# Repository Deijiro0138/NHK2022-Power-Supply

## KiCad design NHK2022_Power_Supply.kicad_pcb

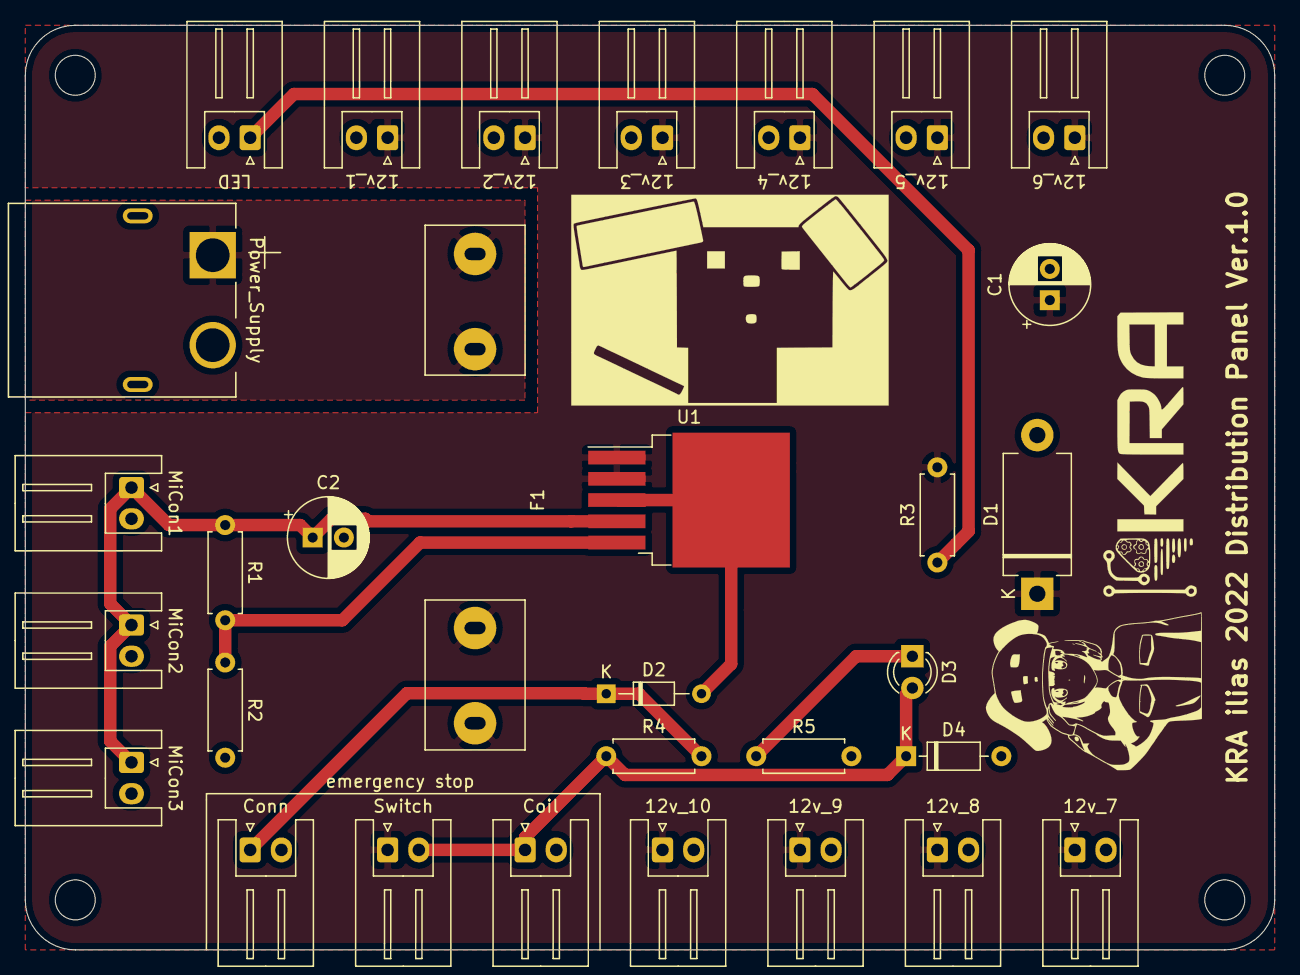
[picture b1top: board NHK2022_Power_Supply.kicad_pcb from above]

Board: 2 copper layers, 100.0 x 74.0 mm, 35 parts (0 on the bottom side), 9 nets.

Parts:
12v_1, 12v_9: XH_MD_1; JST_XH_S2B-XH-A_1x02_P2.50mm_Horizontal
12v_2, 12v_10: XH_MD_2; JST_XH_S2B-XH-A_1x02_P2.50mm_Horizontal
12v_3: XH_MD_3; JST_XH_S2B-XH-A_1x02_P2.50mm_Horizontal
12v_4: XH_MD_4; JST_XH_S2B-XH-A_1x02_P2.50mm_Horizontal
12v_5: XH_MD_5; JST_XH_S2B-XH-A_1x02_P2.50mm_Horizontal
12v_6: XH_MD_6; JST_XH_S2B-XH-A_1x02_P2.50mm_Horizontal
12v_7: XH_MD_7; JST_XH_S2B-XH-A_1x02_P2.50mm_Horizontal
12v_8: XH_MD_8; JST_XH_S2B-XH-A_1x02_P2.50mm_Horizontal
C1, C2: 100u; CP_Radial_D6.3mm_P2.50mm
Coil: coil; JST_XH_S2B-XH-A_1x02_P2.50mm_Horizontal
Conn: Conn_01x02_Male; JST_XH_S2B-XH-A_1x02_P2.50mm_Horizontal
D1: D_Schottky; D_DO-201_P12.70mm_Horizontal
D2: D_Zener; D_DO-34_SOD68_P7.62mm_Horizontal
D3: LED; LED_D3.0mm
D4: D_Schottky; D_DO-35_SOD27_P7.62mm_Horizontal
F1: Fuse; Fuse_Holder
LED: XH_led; JST_XH_S2B-XH-A_1x02_P2.50mm_Horizontal
MiCon1: XH_MiCom_1; JST_XH_S2B-XH-A_1x02_P2.50mm_Horizontal
MiCon2: XH_MiCom_2; JST_XH_S2B-XH-A_1x02_P2.50mm_Horizontal
MiCon3: XH_MiCom_3; JST_XH_S2B-XH-A_1x02_P2.50mm_Horizontal
Power_Supply: XT60; AMASS_XT60PW-M
R1: 3k; R_Axial_DIN0207_L6.3mm_D2.5mm_P7.62mm_Horizontal
R2, R3: 1k; R_Axial_DIN0207_L6.3mm_D2.5mm_P7.62mm_Horizontal
R4: 2k; R_Axial_DIN0207_L6.3mm_D2.5mm_P7.62mm_Horizontal
R5: 680; R_Axial_DIN0207_L6.3mm_D2.5mm_P7.62mm_Horizontal
REF1, REF2, REF3, REF4: MountingHole_3.2mm_M3
Switch: switch; JST_XH_S2B-XH-A_1x02_P2.50mm_Horizontal
U1: TPS75501R; TO-263-5_TabPin3

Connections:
+BATT: F1.1, Power_Supply.1
GND: 12v_1.2, 12v_2.2, 12v_3.2, 12v_4.2, 12v_5.2, 12v_6.2, 12v_7.2, 12v_8.2, 12v_9.2, 12v_10.2, C1.2, C2.2, Coil.2, Conn.2, D1.2, D2.2, D4.2, LED.2, MiCon1.2, MiCon2.2, MiCon3.2, Power_Supply.2, R2.2, R5.2, U1.3
unnamed: C2.1, MiCon1.1, MiCon2.1, MiCon3.1, R1.1, U1.4
unnamed: Conn.1, D2.1, R4.2
unnamed: D3.1, R5.1
unnamed: Coil.1, D3.2, D4.1, R4.1, Switch.2
unnamed: LED.1, R3.1
unnamed: R1.2, R2.1, U1.5
VCC: 12v_1.1, 12v_2.1, 12v_3.1, 12v_4.1, 12v_5.1, 12v_6.1, 12v_7.1, 12v_8.1, 12v_9.1, 12v_10.1, C1.1, D1.1, F1.2, R3.2, Switch.1, U1.1, U1.2
